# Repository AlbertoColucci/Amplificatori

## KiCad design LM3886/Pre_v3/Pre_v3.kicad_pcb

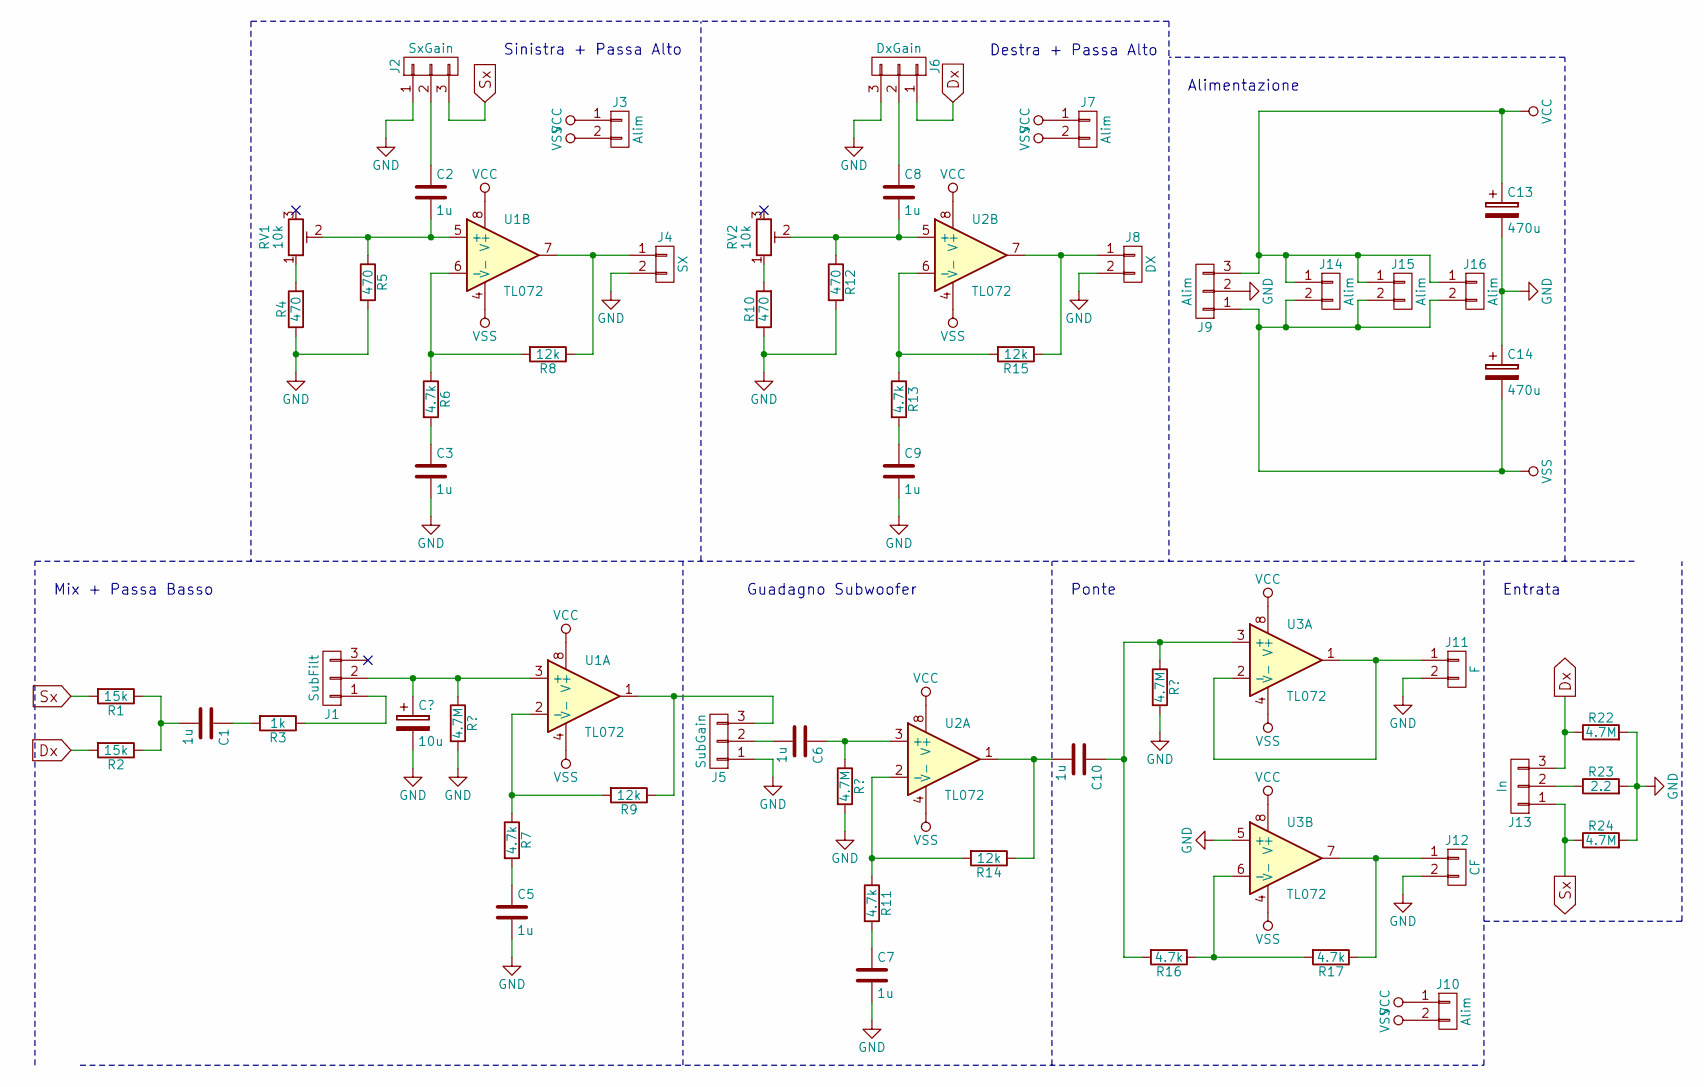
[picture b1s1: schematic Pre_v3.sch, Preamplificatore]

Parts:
C1, C2, C3, C5, C6, C7, C8, C9, C10: 1u; Cap_5x2.7
C13, C14: 470u; Cap_10
J1: SubFilt; 3-Pin
J2: SxGain; 3-Pin
J3, J7, J10, J14, J15, J16: Alim; 2-Pin
J4: SX; AK300-2
J5: SubGain; 3-Pin
J6: DxGain; 3-Pin
J8: DX; AK300-2
J9: Alim; AK300-3
J11: F; AK300-2
J12: CF; AK300-2
J13: In; AK300-3
R1, R2: 15k; Res_Orizz_7mm
R3: 1k; Res_Orizz_7mm
R4, R5, R10, R12: 470; Res_Orizz_7mm
R6, R7, R11, R13, R16, R17: 4.7k; Res_Orizz_7mm
R8, R9, R14, R15: 12k; Res_Orizz_7mm
R22, R24: 4.7M; Res_Orizz_7mm
R23: 2.2; Res_Orizz_7mm
RV1, RV2: 10k; Potentiometer_Trimmer_Bourns_3296W
U1, U2, U3: TL072; DIP-8

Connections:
Dx: J6.1, J13.3, R2.2, R22.1
GND: C3.2, C5.2, C7.2, C9.2, C13.2, C14.1, J2.1, J4.2, J5.1, J6.3, J8.2, J9.2, J11.2, J12.2, R4.1, R5.2, R10.1, R12.2, R22.2, R23.2, R24.2, U3.5 (+); also elsewhere on the board
unnamed: C1.1, R3.2
unnamed: C1.2, R1.1, R2.1
unnamed: C2.1, J2.2
unnamed: C2.2, R5.1, RV1.2, U1.5 (+)
unnamed: C3.1, R6.2
unnamed 7: J1.2, U1.3 (+); also elsewhere on the board
unnamed: C5.1, R7.2
unnamed: C6.1, U2.3 (+)
unnamed: C6.2, J5.2
unnamed: C7.1, R11.2
unnamed: C8.1, J6.2
unnamed: C8.2, R12.1, RV2.2, U2.5 (+)
unnamed: C9.1, R13.2
unnamed: C10.1, R16.2, U3.3 (+)
unnamed: C10.2, R14.1, U2.1
unnamed: J1.1, R3.1
unnamed: J4.1, R8.1, U1.7
unnamed: J5.3, R9.1, U1.1
unnamed: J8.1, R15.1, U2.7
unnamed: J11.1, U3.1, U3.2 (-)
unnamed: J12.1, R17.1, U3.7
unnamed: J13.2, R23.1
unnamed: R4.2, RV1.1
unnamed: R6.1, R8.2, U1.6 (-)
unnamed: R7.1, R9.2, U1.2 (-)
unnamed: R10.2, RV2.1
unnamed: R11.1, R14.2, U2.2 (-)
unnamed: R13.1, R15.2, U2.6 (-)
unnamed: R16.1, R17.2, U3.6 (-)
Sx: J2.3, J13.1, R1.2, R24.1
VCC: C13.1, J3.1, J7.1, J9.3, J10.1, J14.1, J15.1, J16.1, U1.8 (V+), U2.8 (V+), U3.8 (V+)
VSS: C14.2, J3.2, J7.2, J9.1, J10.2, J14.2, J15.2, J16.2, U1.4 (V-), U2.4 (V-), U3.4 (V-)

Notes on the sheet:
Alimentazione
Destra + Passa Alto
Sinistra + Passa Alto
Mix + Passa Basso
Guadagno Subwoofer
Ponte
Entrata

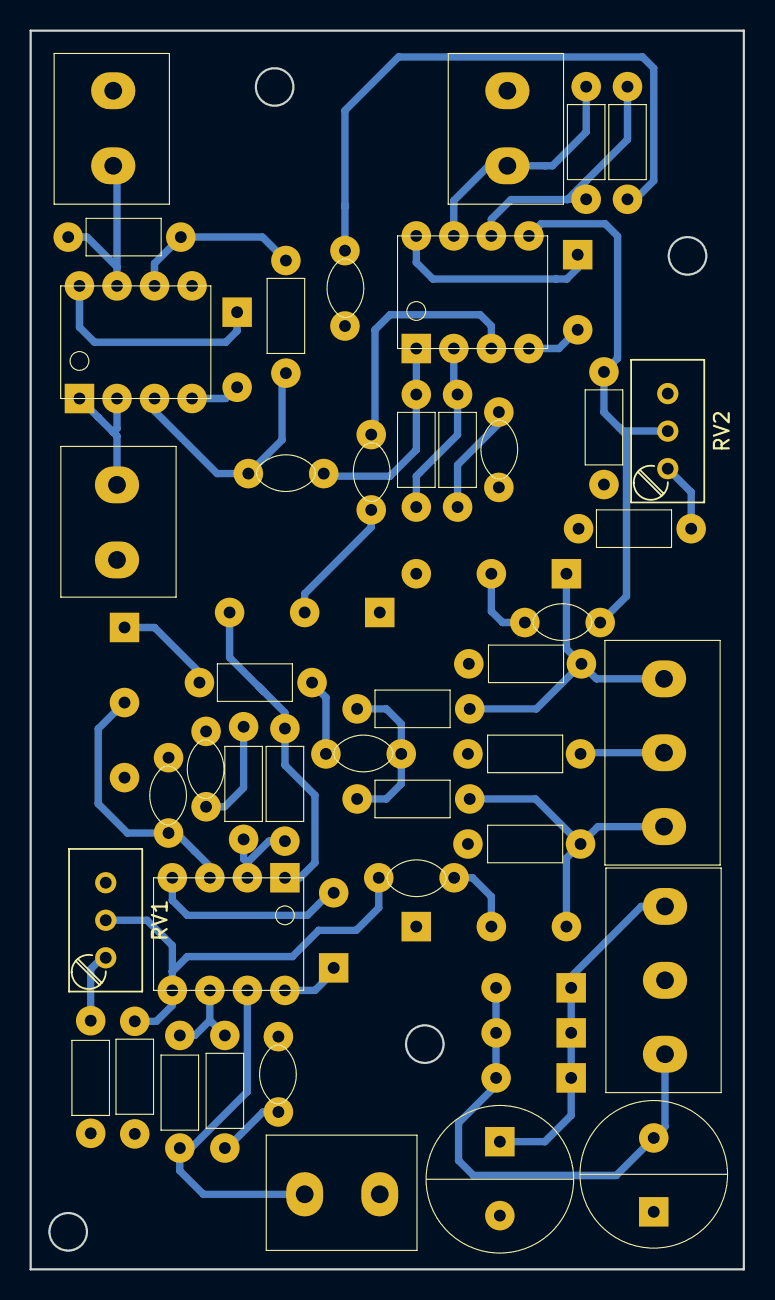
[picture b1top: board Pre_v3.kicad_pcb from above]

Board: 2 copper layers, 48.3 x 83.8 mm, 53 parts (0 on the bottom side), 34 nets.

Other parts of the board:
C4: 1u; Cap_5x2.7

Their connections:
GND: C4.2; also elsewhere on the board
unnamed 7: C4.1; also elsewhere on the board

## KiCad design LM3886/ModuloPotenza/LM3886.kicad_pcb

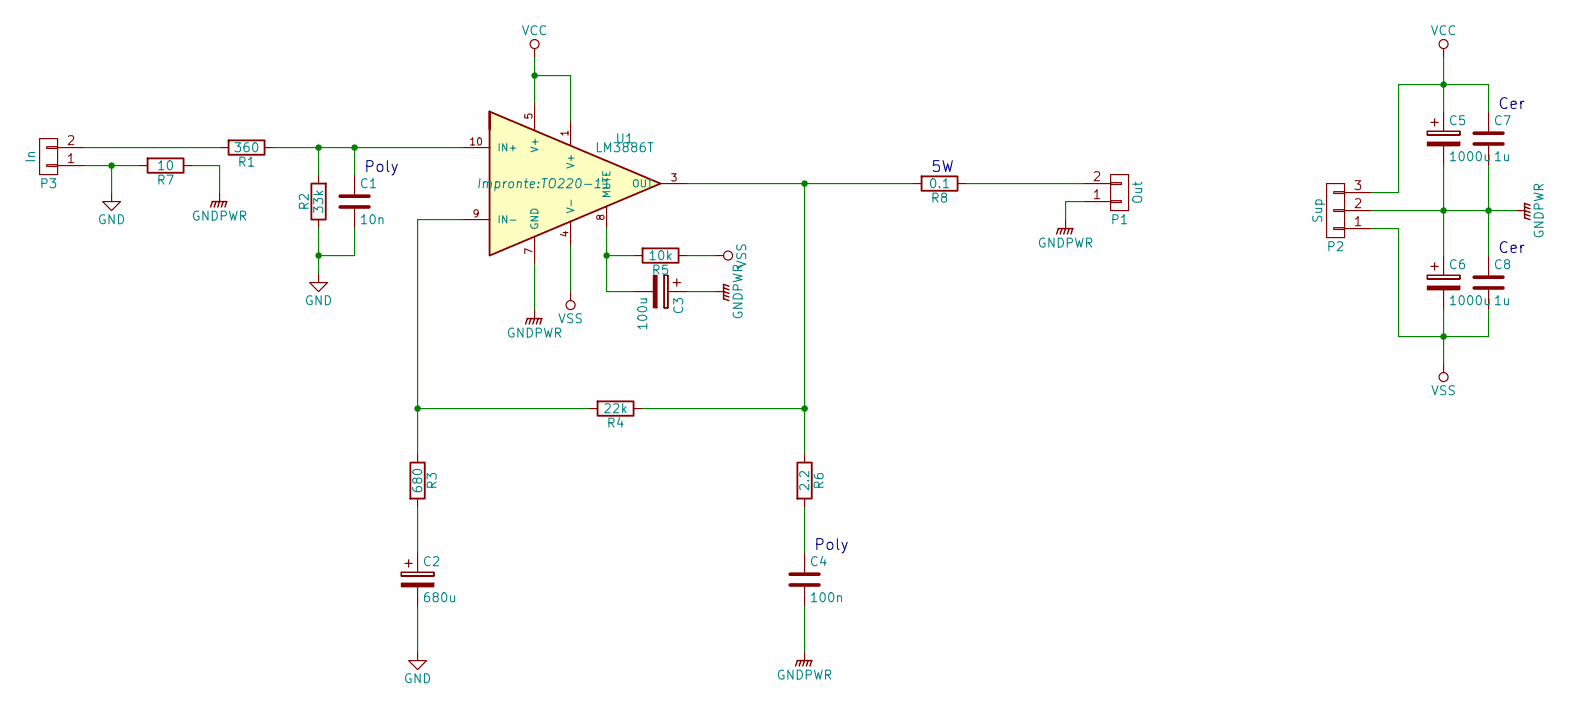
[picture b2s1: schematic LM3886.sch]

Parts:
C1: 10n; Cap_6.3x3.3
C2: 680u; Cap_10
C3: 100u; Cap_6.3
C4: 100n; Cap_6.7x3.7
C5, C6: 1000u; Cap_10
C7, C8: 1u; Cap_5x2.7
P1: Out; AK300-2
P2: Sup; AK300-3
P3: In; AK300-2
R1: 360; Res_Orizz_7mm
R2: 33k; Res_Orizz_7mm
R3: 680; Res_Orizz_7mm
R4: 22k; Res_Orizz_7mm
R5: 10k; Res_Orizz_7mm
R6: 2.2; Res_Orizz_7mm
R7: 10; Res_Orizz_7mm
R8: 0.1; Resistenza_5W_Verticale
U1: LM3886T; TO220-11

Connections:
GND: C1.2, C2.2, P3.1, R2.1, R7.2
GNDPWR: C3.1, C4.2, C5.2, C6.1, C7.2, C8.1, P1.1, P2.2, R7.1, U1.7 (GND)
unnamed: C1.1, R1.1, R2.2, U1.10 (IN+)
unnamed: C2.1, R3.2
unnamed: C3.2, R5.2, U1.8 (MUTE)
unnamed: C4.1, R6.2
unnamed: P1.2, R8.1
unnamed: P3.2, R1.2
unnamed: R3.1, R4.2, U1.9 (IN-)
unnamed: R4.1, R6.1, R8.2, U1.3 (OUT)
VCC: C5.1, C7.1, P2.3, U1.1 (V+), U1.5 (V+)
VSS: C6.2, C8.2, P2.1, R5.1, U1.4 (V-)

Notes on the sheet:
Poly
Poly
Cer

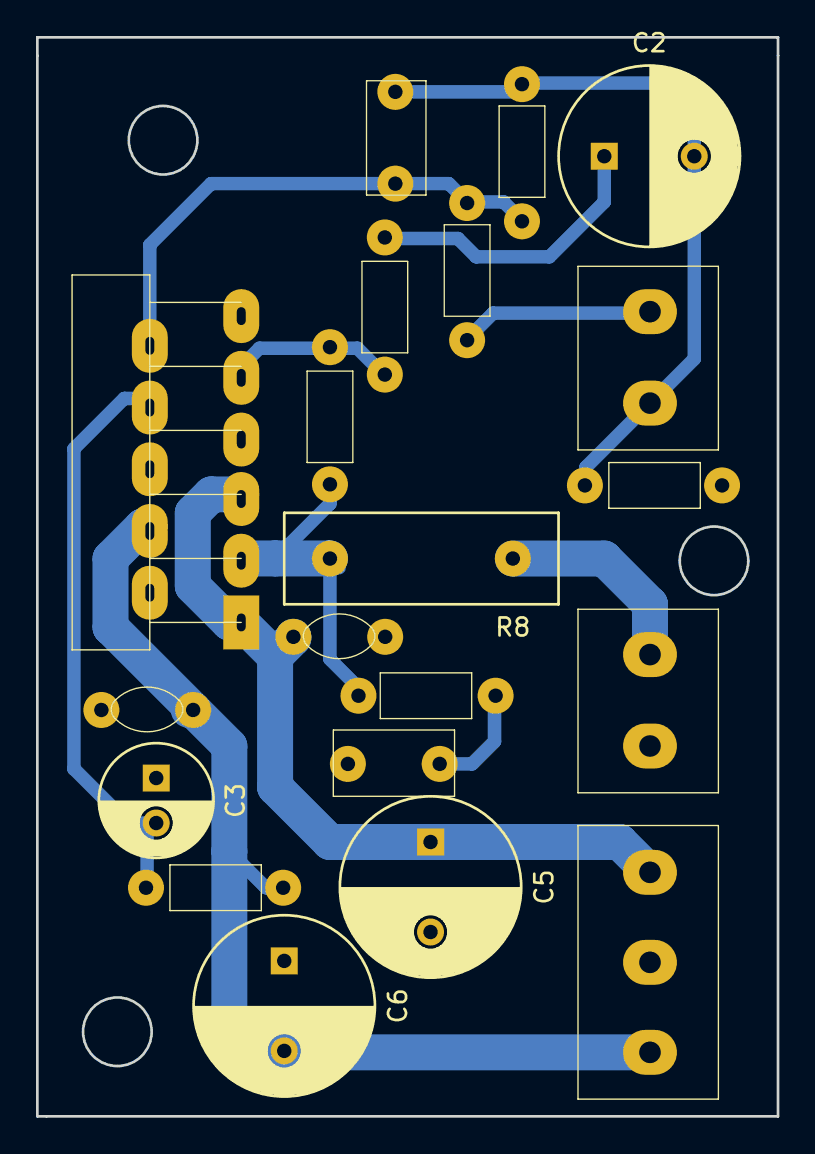
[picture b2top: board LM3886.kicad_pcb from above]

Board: 2 copper layers, 41.1 x 59.9 mm, 20 parts (0 on the bottom side), 12 nets.

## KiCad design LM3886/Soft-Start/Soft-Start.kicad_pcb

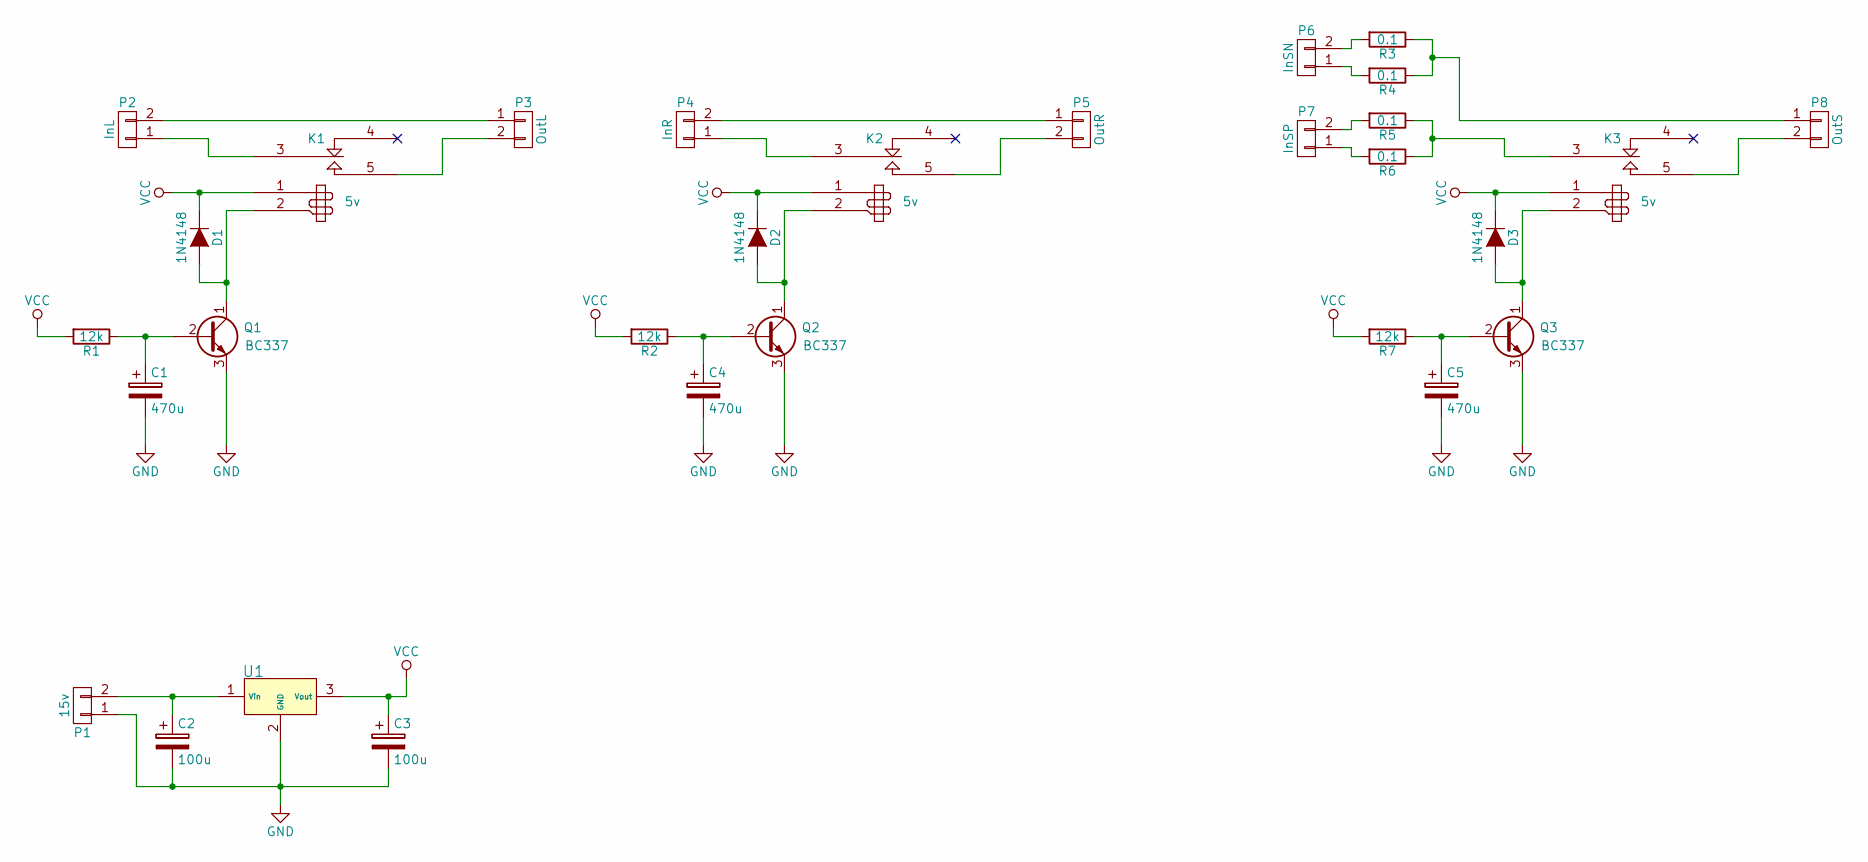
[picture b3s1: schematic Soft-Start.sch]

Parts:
C1, C4, C5: 470u; Cap_10_5.08
C2, C3: 100u; Cap_10_5.08
D1, D2, D3: 1N4148; D_A-405_P7.62mm_Horizontal
K1, K2, K3: 5v; Songle-5V
P1: 15v; AK300-2
P2: InL; AK300-2
P3: OutL; AK300-2
P4: InR; AK300-2
P5: OutR; AK300-2
P6: InSN; AK300-2
P7: InSP; AK300-2
P8: OutS; AK300-2
Q1, Q2, Q3: BC337; TO-92_Largo
R1, R2, R7: 12k; Res_Orizz_10mm
R3, R4, R5, R6: 0.1; Resistenza_5W_Verticale
U1: L780x; TO-220

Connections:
GND: C1.2, C2.2, C3.2, C4.2, C5.2, P1.1, Q1.3 (E), Q2.3 (E), Q3.3 (E), U1.2 (GND)
unnamed: C1.1, Q1.2 (B), R1.1
unnamed: C2.1, P1.2, U1.1 (Vin)
unnamed: C4.1, Q2.2 (B), R2.1
unnamed: C5.1, Q3.2 (B), R7.1
unnamed: D1.2 (A), K1.2, Q1.1 (C)
unnamed: D2.2 (A), K2.2, Q2.1 (C)
unnamed: D3.2 (A), K3.2, Q3.1 (C)
unnamed: K1.3, P2.1
unnamed: K1.5, P3.2
unnamed: K2.3, P4.1
unnamed: K2.5, P5.2
unnamed: K3.3, R5.1, R6.1
unnamed: K3.5, P8.2
unnamed: P2.2, P3.1
unnamed: P4.2, P5.1
unnamed: P6.1, R4.2
unnamed: P6.2, R3.2
unnamed: P7.1, R6.2
unnamed: P7.2, R5.2
unnamed: P8.1, R3.1, R4.1
VCC: C3.1, D1.1 (K), D2.1 (K), D3.1 (K), K1.1, K2.1, K3.1, R1.2, R2.2, R7.2, U1.3 (Vout)

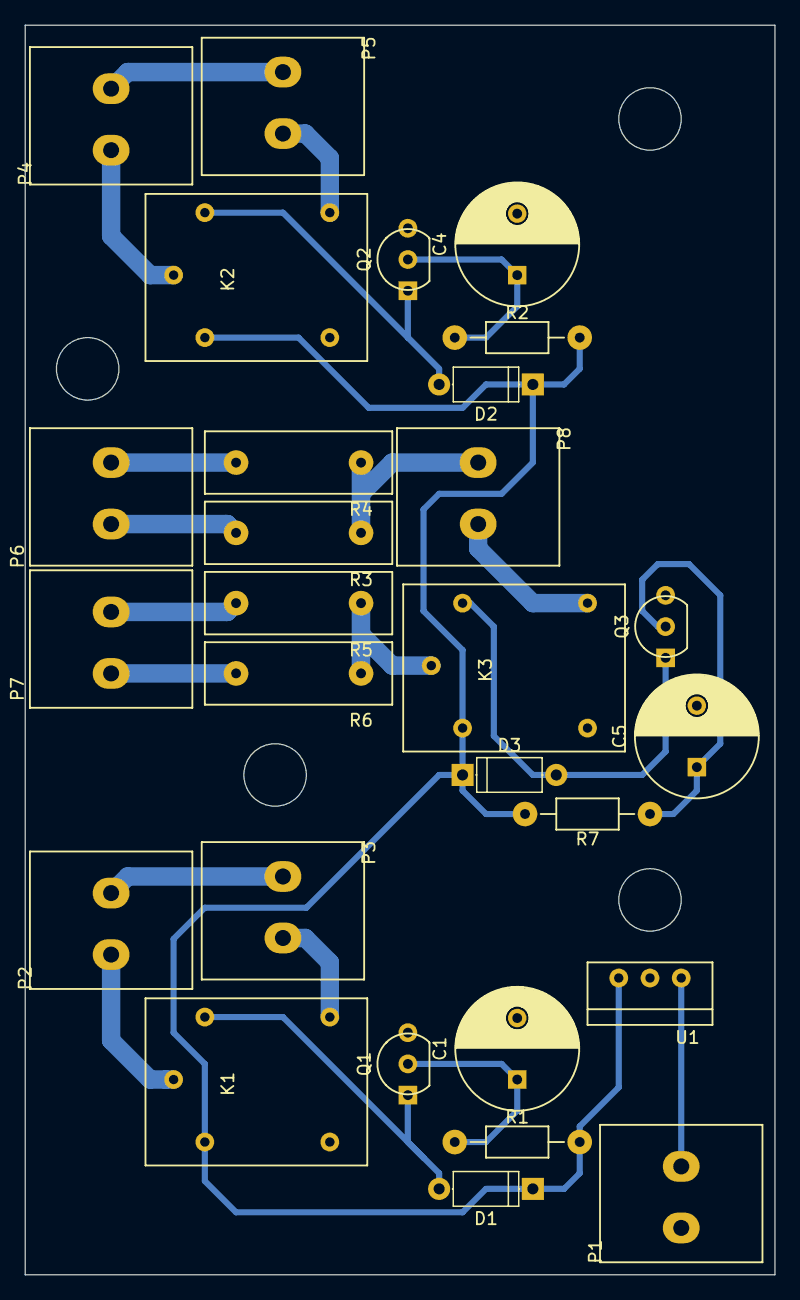
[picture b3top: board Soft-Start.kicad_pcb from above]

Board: 2 copper layers, 61.0 x 101.6 mm, 28 parts (0 on the bottom side), 22 nets.

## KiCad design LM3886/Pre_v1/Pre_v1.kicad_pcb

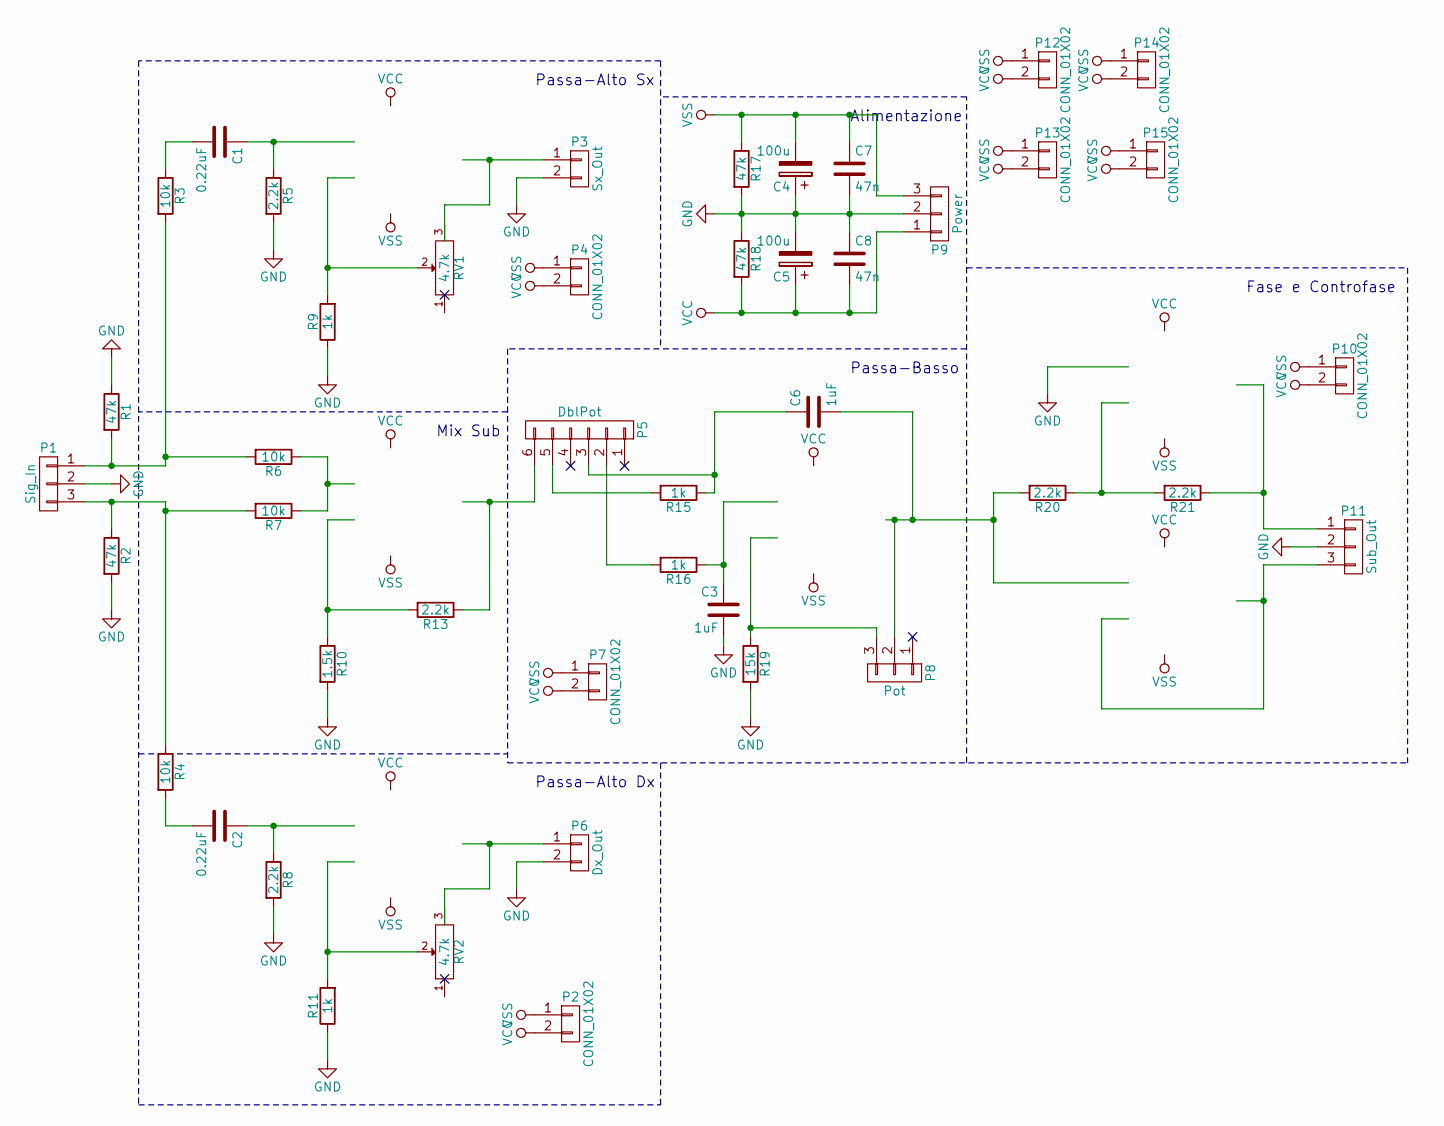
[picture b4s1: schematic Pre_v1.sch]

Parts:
C1, C2: 0.22uF; C_Rect_L7.0mm_W2.0mm_P5.00mm
C3, C6: 1uF; C_Rect_L7.0mm_W6.5mm_P5.00mm
C4, C5: 100u; CP_Radial_D8.0mm_P2.50mm
C7, C8: 47n; C_Rect_L7.0mm_W2.0mm_P5.00mm
P1: Sig_In; AK300-3
P2, P4, P7, P10, P12, P13, P14, P15: CONN_01X02; 2-Pin
P3: Sx_Out; AK300-2
P5: DblPot; 6-Pin
P6: Dx_Out; AK300-2
P8: Pot; 3-Pin
P9: Power; AK300-3
P11: Sub_Out; AK300-3
R1, R2, R17, R18: 47k; Res_Orizz_10mm
R3, R4, R6, R7: 10k; Res_Orizz_10mm
R5, R8, R13, R20, R21: 2.2k; Res_Orizz_10mm
R9, R11, R15, R16: 1k; Res_Orizz_10mm
R10: 1.5k; Res_Orizz_10mm
R19: 15k; Res_Orizz_10mm
RV1, RV2: 4.7k; Potentiometer_Trimmer_ACP_CA9h2.5_Vertical_Px2.5mm_Py5.0mm

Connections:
GND: C3.2, C4.1, C5.2, C7.2, C8.1, P1.2, P3.2, P6.2, P9.2, P11.2, R1.1, R2.2, R5.2, R8.2, R9.1, R10.2, R11.1, R17.2, R18.1, R19.2; also elsewhere on the board
unnamed 1: C1.1, R5.1; also elsewhere on the board
unnamed: C1.2, R3.1
unnamed 3: C2.1, R8.1; also elsewhere on the board
unnamed: C2.2, R4.2
unnamed 5: C3.1, R16.1; also elsewhere on the board
unnamed: C6.1, P5.3, R15.1
unnamed 7: C6.2, P8.2, R20.2; also elsewhere on the board
unnamed: P1.1, R1.2, R3.2, R6.2
unnamed: P1.3, R2.1, R4.1, R7.2
unnamed 10: P3.1, RV1.3; also elsewhere on the board
unnamed: P5.2, R16.2
unnamed: P5.5, R15.2
unnamed 13: P5.6, R13.1; also elsewhere on the board
unnamed 14: P6.1, RV2.3; also elsewhere on the board
unnamed 15: P8.3, R19.1; also elsewhere on the board
unnamed 16: P11.1, R21.1; also elsewhere on the board
unnamed 17: P11.3; also elsewhere on the board
unnamed 18: R6.1, R7.1; also elsewhere on the board
unnamed 19: R9.2, RV1.2; also elsewhere on the board
unnamed 20: R10.1, R13.2; also elsewhere on the board
unnamed 21: R11.2, RV2.2; also elsewhere on the board
unnamed 22: R20.1, R21.2; also elsewhere on the board
VCC: C5.1, C8.2, P2.2, P4.2, P7.2, P9.1, P10.2, P12.2, P13.2, P14.2, P15.2, R18.2; also elsewhere on the board
VSS: C4.2, C7.1, P2.1, P4.1, P7.1, P9.3, P10.1, P12.1, P13.1, P14.1, P15.1, R17.1; also elsewhere on the board

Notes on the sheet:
Fase e Controfase
Alimentazione
Passa-Alto Sx
Passa-Alto Dx
Mix Sub
Passa-Basso

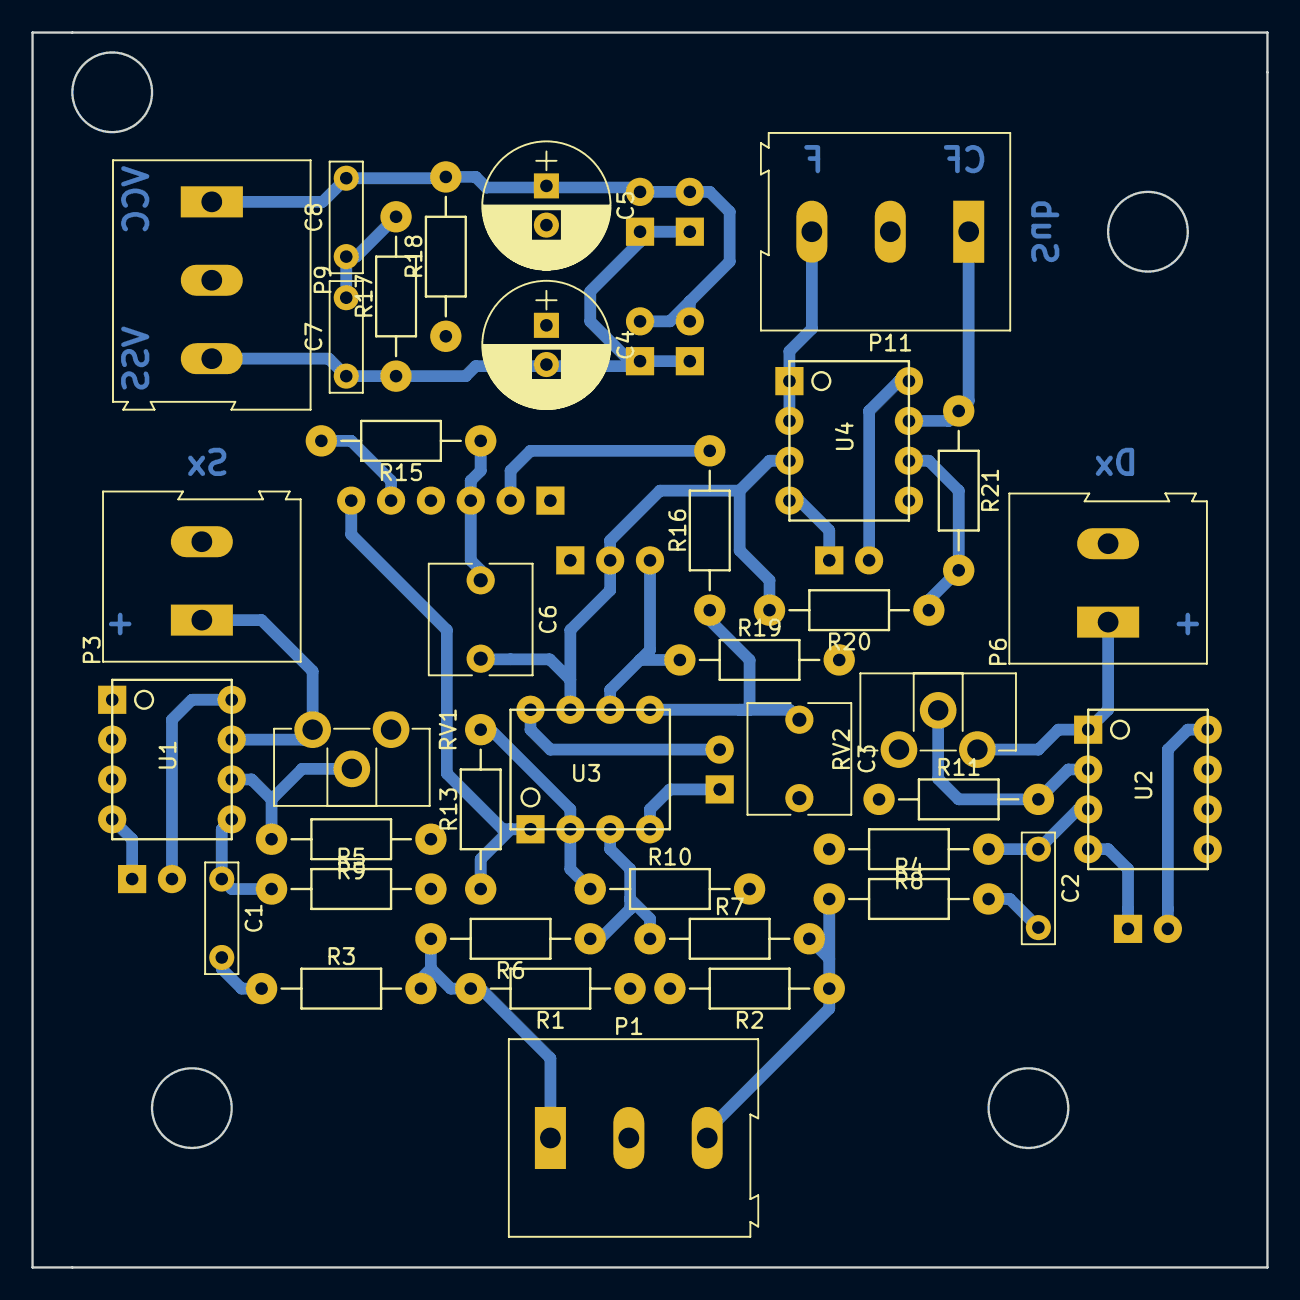
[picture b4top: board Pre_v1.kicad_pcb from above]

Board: 2 copper layers, 78.7 x 78.7 mm, 48 parts (0 on the bottom side), 25 nets.

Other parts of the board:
U1, U2, U3, U4: LM358; DIP-8

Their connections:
GND: U4.5; also elsewhere on the board
unnamed 1: U1.5; also elsewhere on the board
unnamed 3: U2.3; also elsewhere on the board
unnamed 5: U3.5; also elsewhere on the board
unnamed 7: U3.7, U4.3; also elsewhere on the board
unnamed 10: U1.7; also elsewhere on the board
unnamed 13: U3.1; also elsewhere on the board
unnamed 14: U2.1; also elsewhere on the board
unnamed 15: U3.6; also elsewhere on the board
unnamed 16: U4.7; also elsewhere on the board
unnamed 17: U4.1, U4.2; also elsewhere on the board
unnamed 18: U3.3; also elsewhere on the board
unnamed 19: U1.6; also elsewhere on the board
unnamed 20: U3.2; also elsewhere on the board
unnamed 21: U2.2; also elsewhere on the board
unnamed 22: U4.6; also elsewhere on the board
VCC: U1.8, U2.8, U3.8, U4.8; also elsewhere on the board
VSS: U1.4, U2.4, U3.4, U4.4; also elsewhere on the board

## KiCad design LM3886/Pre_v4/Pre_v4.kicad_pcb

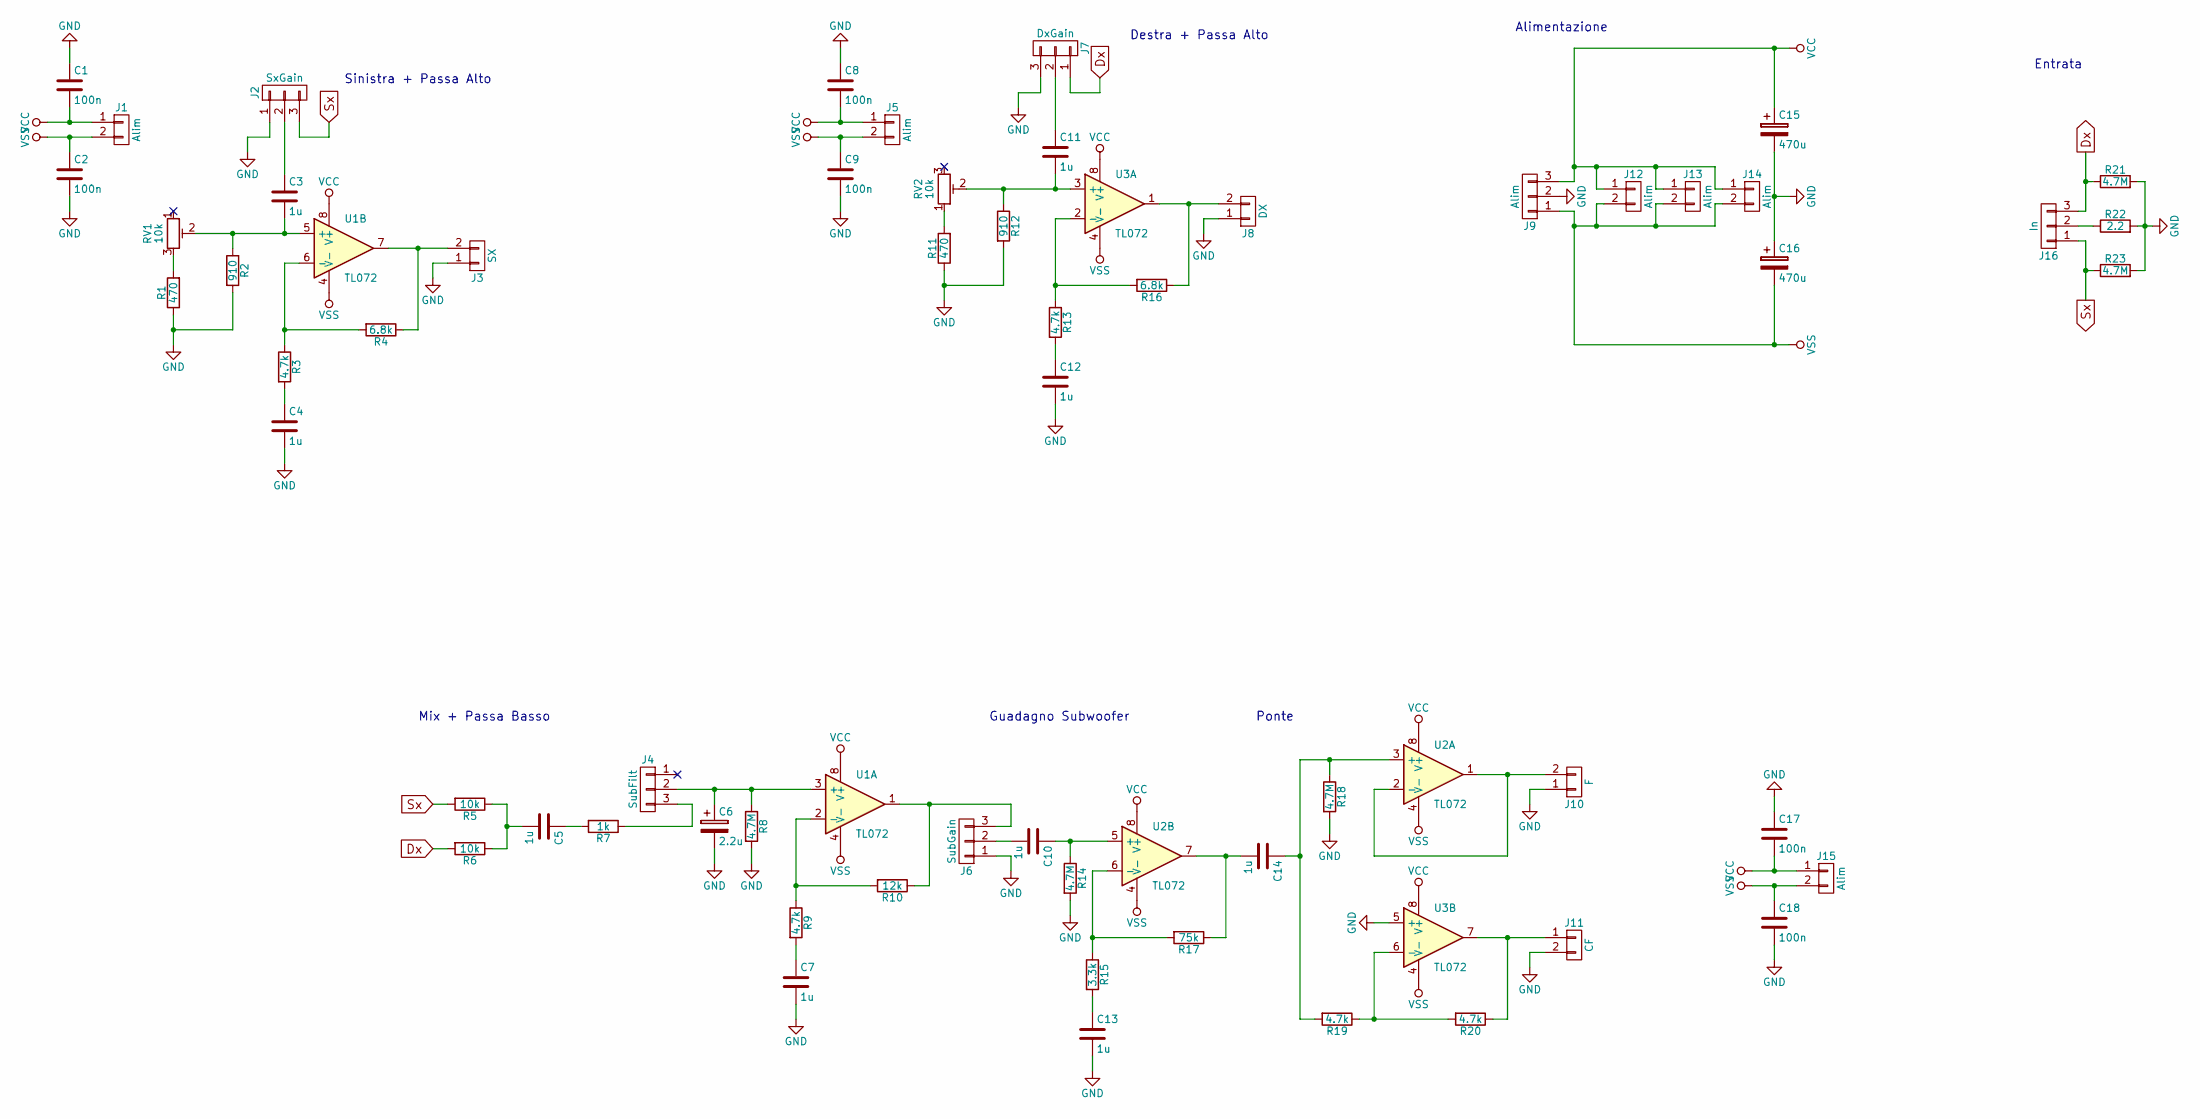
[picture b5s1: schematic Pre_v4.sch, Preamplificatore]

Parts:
C1, C2, C8, C9, C17, C18: 100n; Cap_5x2.7
C3, C4, C5, C7, C10, C11, C12, C13, C14: 1u; Cap_5x2.7
C6: 2.2u; Cap_6.3
C15, C16: 470u; Cap_10
J1, J5, J12, J13, J14, J15: Alim; 2-Pad
J2: SxGain; 3-Pin
J3: SX; AK300-2
J4: SubFilt; 3-Pin
J6: SubGain; 3-Pin
J7: DxGain; 3-Pin
J8: DX; AK300-2
J9: Alim; AK300-3
J10: F; AK300-2
J11: CF; AK300-2
J16: In; AK300-3
R1, R11: 470; Res_Orizz_7mm
R2, R12: 910; Res_Orizz_7mm
R3, R9, R13, R19, R20: 4.7k; Res_Orizz_7mm
R4, R16: 6.8k; Res_Orizz_7mm
R5, R6: 10k; Res_Orizz_7mm
R7: 1k; Res_Orizz_7mm
R8, R14, R18, R21, R23: 4.7M; Res_Orizz_7mm
R10: 12k; Res_Orizz_7mm
R15: 3.3k; Res_Orizz_7mm
R17: 75k; Res_Orizz_7mm
R22: 2.2; Res_Orizz_7mm
RV1, RV2: 10k; Trimmer_Cermet_3296
U1, U2, U3: TL072; DIP-8

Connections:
Dx: J7.1, J16.3, R6.2, R21.1
GND: C1.1, C2.2, C4.2, C6.2, C7.2, C8.1, C9.2, C12.2, C13.2, C15.2, C16.1, C17.1, C18.2, J2.1, J3.1, J6.1, J7.3, J8.1, J9.2, J10.1, J11.2, R1.1, R2.2, R8.2, R11.1, R12.2, R14.2, R18.2, R21.2, R22.2, R23.2, U3.5 (+)
unnamed: C3.1, J2.2
unnamed: C3.2, R2.1, RV1.2, U1.5 (+)
unnamed: C4.1, R3.2
unnamed: C5.1, R7.2
unnamed: C5.2, R5.1, R6.1
unnamed: C6.1, J4.2, R8.1, U1.3 (+)
unnamed: C7.1, R9.2
unnamed: C10.1, R14.1, U2.5 (+)
unnamed: C10.2, J6.2
unnamed: C11.1, J7.2
unnamed: C11.2, R12.1, RV2.2, U3.3 (+)
unnamed: C12.1, R13.2
unnamed: C13.1, R15.2
unnamed: C14.1, R18.1, R19.2, U2.3 (+)
unnamed: C14.2, R17.1, U2.7
unnamed: J3.2, R4.1, U1.7
unnamed: J4.3, R7.1
unnamed: J6.3, R10.1, U1.1
unnamed: J8.2, R16.1, U3.1
unnamed: J10.2, U2.1, U2.2 (-)
unnamed: J11.1, R20.1, U3.7
unnamed: J16.2, R22.1
unnamed: R1.2, RV1.3
unnamed: R3.1, R4.2, U1.6 (-)
unnamed: R9.1, R10.2, U1.2 (-)
unnamed: R11.2, RV2.1
unnamed: R13.1, R16.2, U3.2 (-)
unnamed: R15.1, R17.2, U2.6 (-)
unnamed: R19.1, R20.2, U3.6 (-)
Sx: J2.3, J16.1, R5.2, R23.1
VCC: C1.2, C8.2, C15.1, C17.2, J1.1, J5.1, J9.3, J12.1, J13.1, J14.1, J15.1, U1.8 (V+), U2.8 (V+), U3.8 (V+)
VSS: C2.1, C9.1, C16.2, C18.1, J1.2, J5.2, J9.1, J12.2, J13.2, J14.2, J15.2, U1.4 (V-), U2.4 (V-), U3.4 (V-)

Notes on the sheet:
Alimentazione
Destra + Passa Alto
Sinistra + Passa Alto
Mix + Passa Basso
Guadagno Subwoofer
Ponte
Entrata

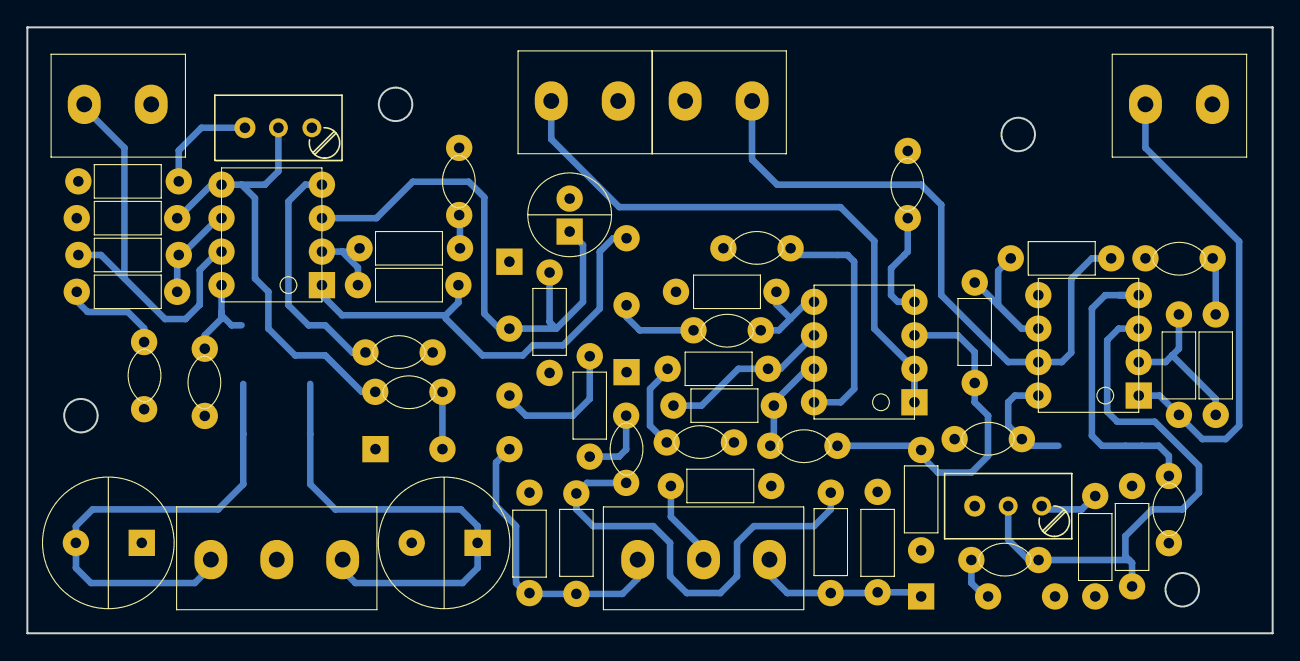
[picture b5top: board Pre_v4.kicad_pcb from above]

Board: 2 copper layers, 94.5 x 46.0 mm, 62 parts (0 on the bottom side), 34 nets.

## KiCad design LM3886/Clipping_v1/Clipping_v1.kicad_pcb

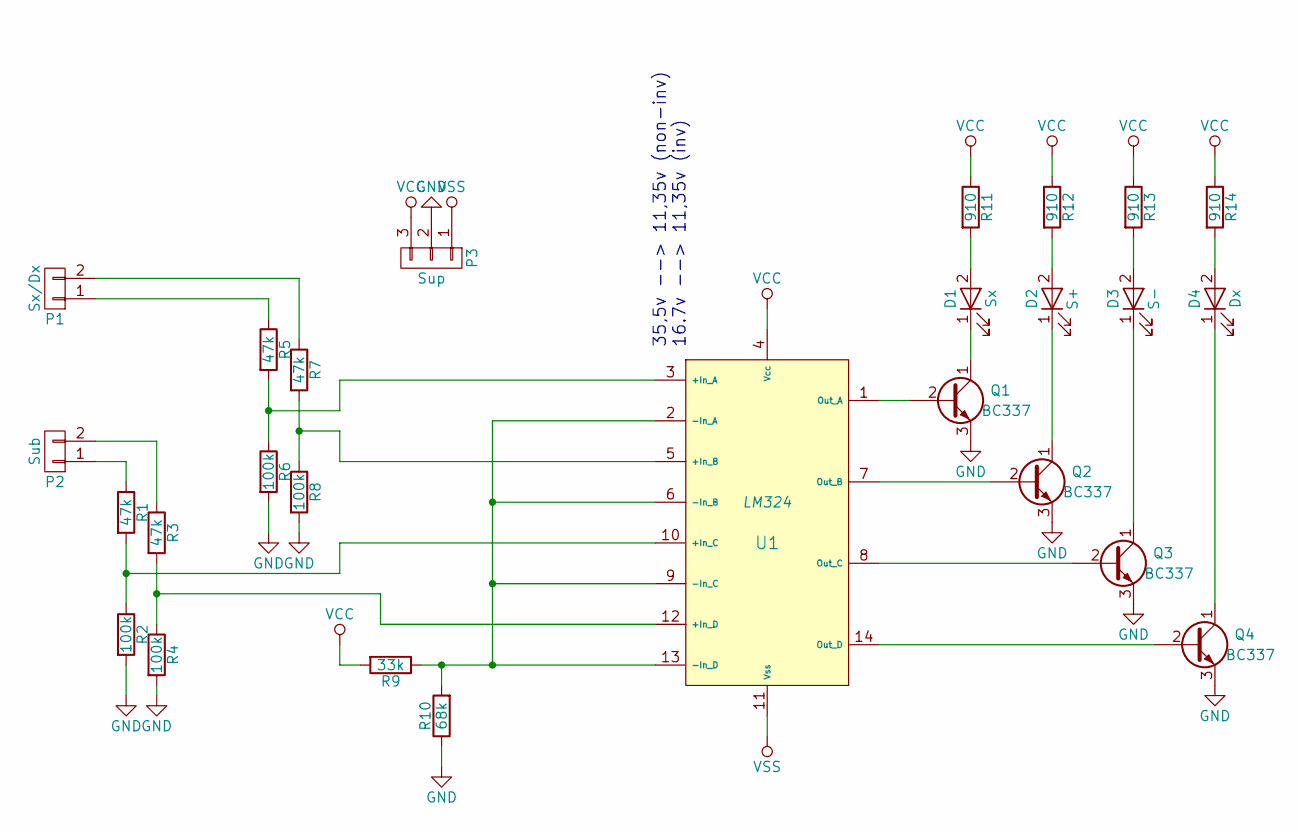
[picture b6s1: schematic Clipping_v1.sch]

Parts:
D1: Sx; LED_D3.0mm
D2: S+; LED_D3.0mm
D3: S-; LED_D3.0mm
D4: Dx; LED_D3.0mm
P1: Sx/Dx; AK300-2
P2: Sub; AK300-2
P3: Sup; AK300-3
Q1, Q2, Q3, Q4: BC337; TO-92_Largo
R1, R3, R5, R7: 47k; Res_Orizz_7mm
R2, R4, R6, R8: 100k; Res_Orizz_7mm
R9: 33k; Res_Orizz_7mm
R10: 68k; Res_Orizz_7mm
R11, R12, R13, R14: 910; Res_Orizz_7mm
U1: LM324; DIP-14

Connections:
GND: P3.2, Q1.3 (E), Q2.3 (E), Q3.3 (E), Q4.3 (E), R2.2, R4.2, R6.2, R8.2, R10.1
unnamed: D1.1 (K), Q1.1 (C)
unnamed: D1.2 (A), R11.2
unnamed: D2.1 (K), Q2.1 (C)
unnamed: D2.2 (A), R12.2
unnamed: D3.1 (K), Q3.1 (C)
unnamed: D3.2 (A), R13.2
unnamed: D4.1 (K), Q4.1 (C)
unnamed: D4.2 (A), R14.2
unnamed: P1.1, R5.1
unnamed: P1.2, R7.1
unnamed: P2.1, R1.1
unnamed: P2.2, R3.1
unnamed: Q1.2 (B), U1.1 (Out_A)
unnamed: Q2.2 (B), U1.7 (Out_B)
unnamed: Q3.2 (B), U1.8 (Out_C)
unnamed: Q4.2 (B), U1.14 (Out_D)
unnamed: R1.2, R2.1, U1.10 (+In_C)
unnamed: R3.2, R4.1, U1.12 (+In_D)
unnamed: R5.2, R6.1, U1.3 (+In_A)
unnamed: R7.2, R8.1, U1.5 (+In_B)
unnamed: R9.1, R10.2, U1.2 (-In_A), U1.6 (-In_B), U1.9 (-In_C), U1.13 (-In_D)
VCC: P3.3, R9.2, R11.1, R12.1, R13.1, R14.1, U1.4 (Vcc)
VSS: P3.1, U1.11 (Vss)

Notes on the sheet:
35,5v --> 11,35v (non-inv) 16.7v --> 11,35v (inv)

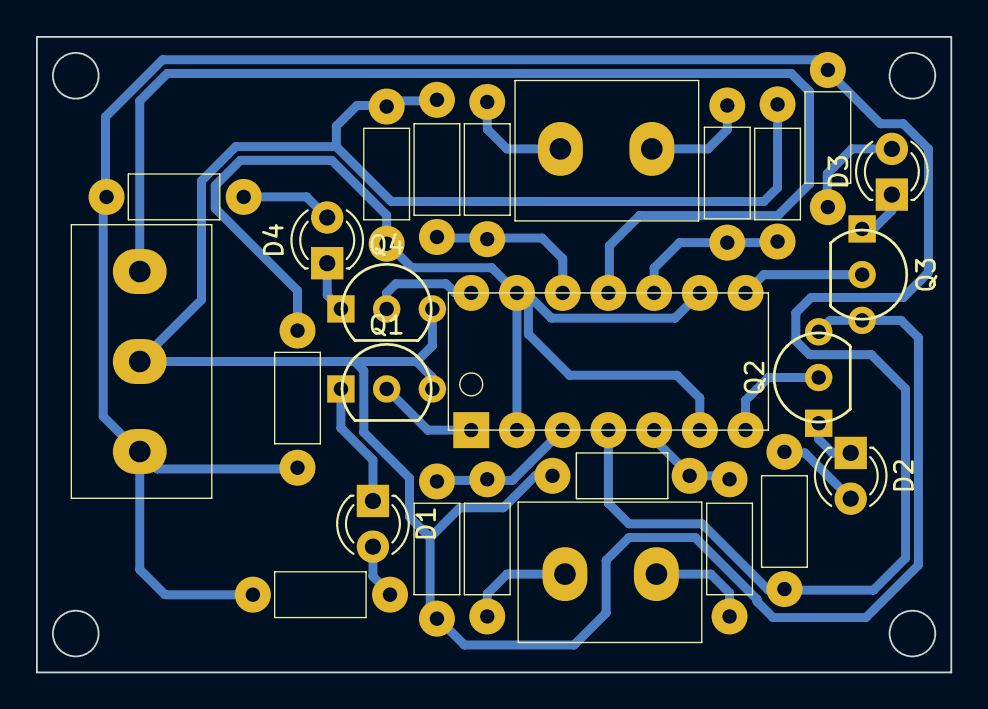
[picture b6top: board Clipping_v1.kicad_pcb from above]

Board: 2 copper layers, 50.8 x 35.3 mm, 26 parts (0 on the bottom side), 24 nets.
